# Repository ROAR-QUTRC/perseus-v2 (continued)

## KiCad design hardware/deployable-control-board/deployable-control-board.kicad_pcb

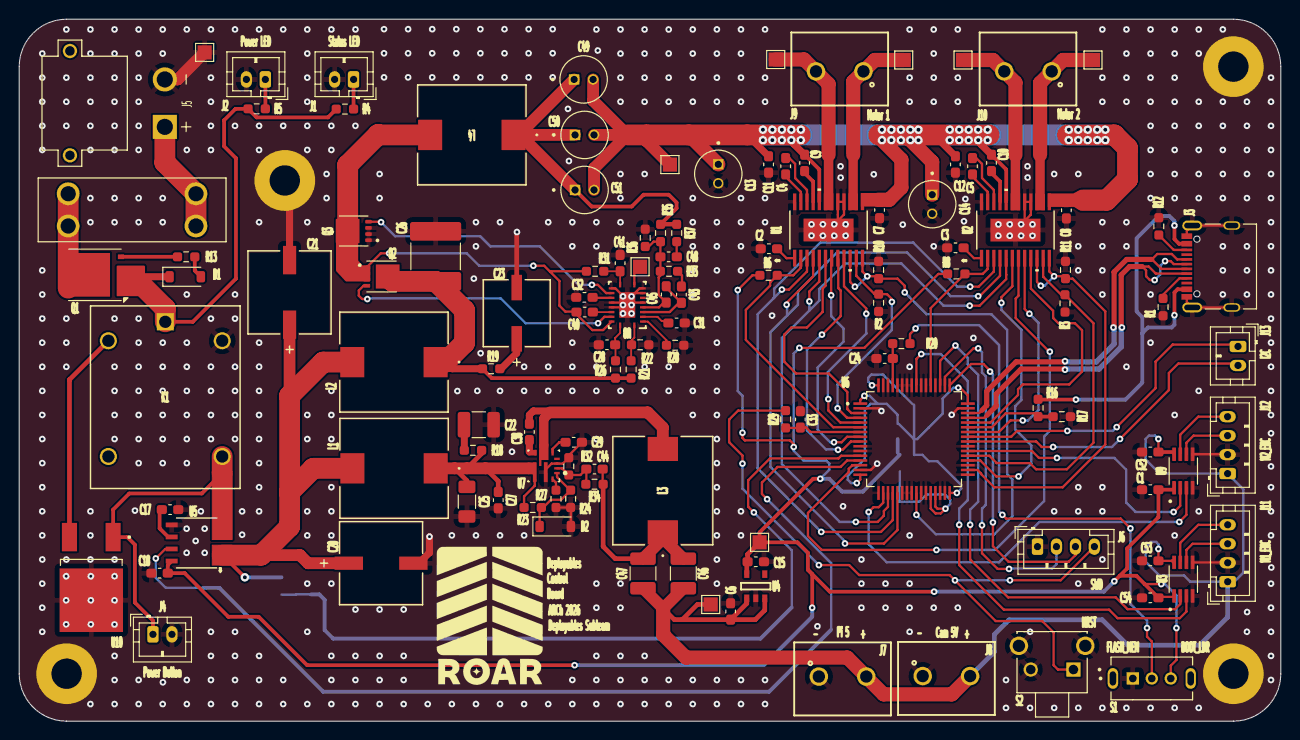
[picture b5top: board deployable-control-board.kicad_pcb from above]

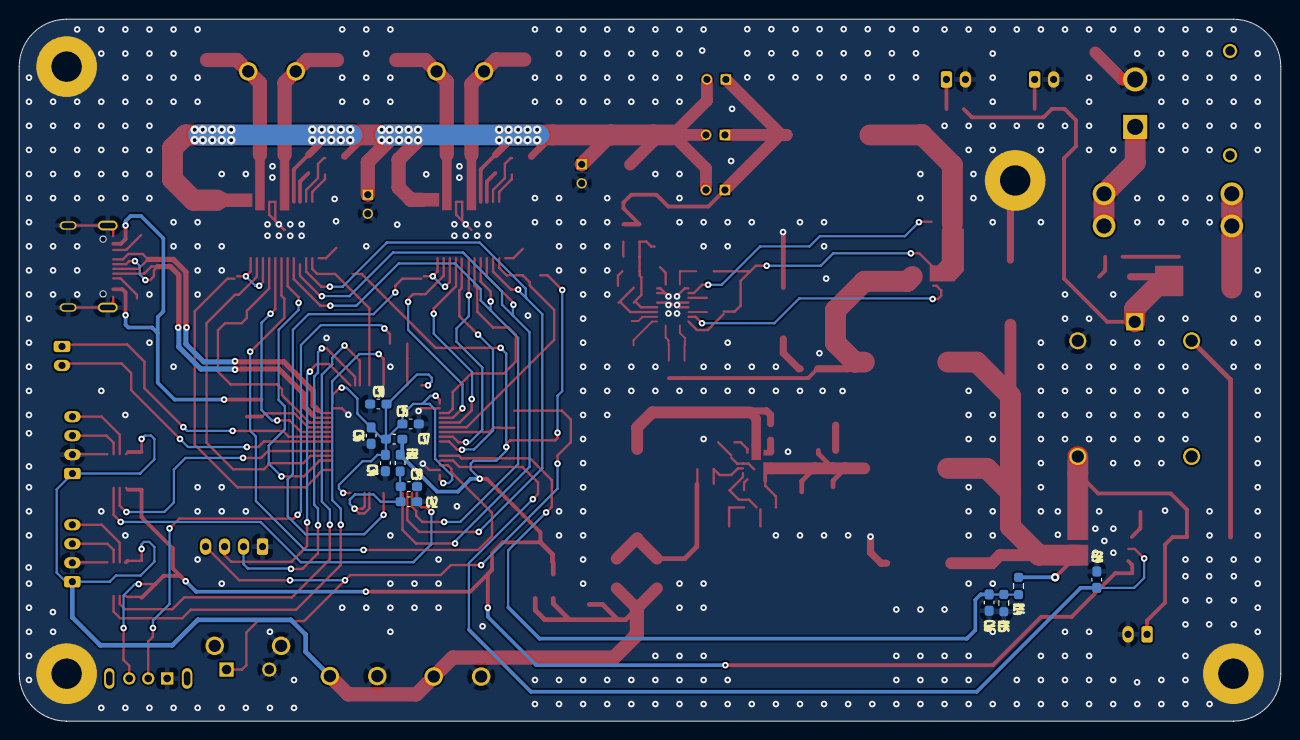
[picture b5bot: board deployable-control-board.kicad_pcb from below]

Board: 2 copper layers, 133.0 x 74.0 mm, 135 parts (12 on the bottom side), 97 nets.

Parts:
3.2mm, 3.2mm#2: MountingHole_3.2mm_M3_Pad
C1, C7, C8, C11, C16, C18, C24, C28, C30, C33, C34, C35, C36, C38, C39, C40, C52, C53, C54: 100n; C_0603_1608Metric_Pad1.08x0.95mm_HandSolder
C2, C3, C6, C9, C10, C12, C15, C27, C42: 1u; C_0603_1608Metric_Pad1.08x0.95mm_HandSolder
C4, C5: 47n; C_0603_1608Metric_Pad1.08x0.95mm_HandSolder
C13, C14, C49, C50, C51: 22u; CAPPRD200W50D500H1100
C17: 1n; C_0603_1608Metric_Pad1.08x0.95mm_HandSolder
C19: 10n; C_0603_1608Metric_Pad1.08x0.95mm_HandSolder
C20, C21: 180u; PCAP_SVP_E12_PAN-L
C22: 10u; C_1210_3225Metric_Pad1.33x2.70mm_HandSolder
C23: 47u; PCAP_SVP_C6_PAN-L
C25: 15u; C_1206_3216Metric_Pad1.33x1.80mm_HandSolder
C26: 15u; C_2220_5750Metric_Pad1.97x5.40mm_HandSolder
C29: 22n; C_0603_1608Metric_Pad1.08x0.95mm_HandSolder
C31: 56n; C_0603_1608Metric_Pad1.08x0.95mm_HandSolder
C32: 2u2; C_0603_1608Metric_Pad1.08x0.95mm_HandSolder
C37: 4u7; C_0603_1608Metric_Pad1.08x0.95mm_HandSolder
C41: 10p; C_0603_1608Metric_Pad1.08x0.95mm_HandSolder
C43: 12n; C_0603_1608Metric_Pad1.08x0.95mm_HandSolder
C44: 150p; C_0603_1608Metric_Pad1.08x0.95mm_HandSolder
C45: 1n5; C_0603_1608Metric_Pad1.08x0.95mm_HandSolder
C46, C47: 22u; C_1210_3225Metric_Pad1.33x2.70mm_HandSolder
C48: 560p; C_0603_1608Metric_Pad1.08x0.95mm_HandSolder
D1: 12V; D_SOD-123
D2: D_Zener; D_SOD-123
F1: 20A; FUSE_3557-10
FB1: FerriteBead; L_0603_1608Metric_Pad1.05x0.95mm_HandSolder
J1: Status LED; JST_PH_B2B-PH-K_1x02_P2.00mm_Vertical
J2: Power LED; JST_PH_B2B-PH-K_1x02_P2.00mm_Vertical
J3: 12402012E212A; AMPHENOL_12402012E212A
J4: Power Button; JST_PH_B2B-PH-K_1x02_P2.00mm_Vertical
J5: XT30PW-M; AMASS_XT30PW-M
J6: SWD; JST_PH_B4B-PH-K_1x04_P2.00mm_Vertical
J7: RPi_PWR; 691137710002
J8: CAMERA; 691137710002
J9: M1_PWR; 691137710002
J10: M2_PWR; 691137710002
J11: M1_ENC; JST_PH_B4B-PH-K_1x04_P2.00mm_Vertical
J12: M2_ENC; JST_PH_B4B-PH-K_1x04_P2.00mm_Vertical
J13: I2C; JST_PH_B2B-PH-K_1x02_P2.00mm_Vertical
K1: J107F1CS125VDC.36; RELAY5_J107F-1C_CRS
L1: 4u7; IND_IHLP-4040DZ_VIS-L
L2: 1u8; IND_IHLP-4040DZ_VIS-L
L3: 3u3; IND_IHLP-4040DZ_VIS-L
L4: 5u6; IND_IHLP-4040DZ_VIS-L
Q1: AON6411; AO_DFN-8-1EP_5.55x5.2mm_P1.27mm_EP4.12x4.6mm
Q2: CSD17577Q3A; MOSFET_CSD17577Q3A
Q3: CSD17578Q3A; TRANS_CSD18543Q3A
R1, R12: 5k1; R_0603_1608Metric_Pad0.98x0.95mm_HandSolder
R2, R3: DNP; R_0603_1608Metric_Pad0.98x0.95mm_HandSolder
R4: R; R_0603_1608Metric_Pad0.98x0.95mm_HandSolder
R5: 470; R_0603_1608Metric_Pad0.98x0.95mm_HandSolder
R6, R8, R14, R17, R20, R32: 10k; R_0603_1608Metric_Pad0.98x0.95mm_HandSolder
R10, R11: 360; R_0603_1608Metric_Pad0.98x0.95mm_HandSolder
R13: 22k; R_0603_1608Metric_Pad0.98x0.95mm_HandSolder
R15: 3k9; R_0603_1608Metric_Pad0.98x0.95mm_HandSolder
R16: 4k7; R_0603_1608Metric_Pad0.98x0.95mm_HandSolder
R18: 1; R_0603_1608Metric_Pad0.98x0.95mm_HandSolder
R19: 360m; R_0603_1608Metric_Pad0.98x0.95mm_HandSolder
R21: 68k1; R_0603_1608Metric_Pad0.98x0.95mm_HandSolder
R22: 9k1; R_0603_1608Metric_Pad0.98x0.95mm_HandSolder
R23: 3k09; R_0603_1608Metric_Pad0.98x0.95mm_HandSolder
R24: 294; R_0603_1608Metric_Pad0.98x0.95mm_HandSolder
R26: 2R1; R_0603_1608Metric_Pad0.98x0.95mm_HandSolder
R27: 52k3; R_0603_1608Metric_Pad0.98x0.95mm_HandSolder
R28: 59k; R_0603_1608Metric_Pad0.98x0.95mm_HandSolder
R29: 100; R_0603_1608Metric_Pad0.98x0.95mm_HandSolder
R31: 787; R_0603_1608Metric_Pad0.98x0.95mm_HandSolder
R33: 1k37; R_0603_1608Metric_Pad0.98x0.95mm_HandSolder
R34: 73k2; R_0603_1608Metric_Pad0.98x0.95mm_HandSolder
R35: 18k; R_0603_1608Metric_Pad0.98x0.95mm_HandSolder
R36: 1k27; R_0603_1608Metric_Pad0.98x0.95mm_HandSolder
R37: 41R2; R_0603_1608Metric_Pad0.98x0.95mm_HandSolder
S1: BOOT_SEL; SW_SLW-864587-2A-RA-N-D
S2: NRST; SW_TS11-674-50-BK-260-RA-D
TP1, TP2, TP3, TP4, TP5, TP6, TP7, TP9, TP10: TestPoint; TestPoint_Pad_1.5x1.5mm
U1, U2: DRV8873SPWPR; PWP24_TEX-M
U3, U9: SN74LVC2T45DCTR; SOP65P400X130-8N
U4: TLV75533PDBVR
U5: ACS725LLCTR-20AB-T; SOICN8_LC_ALM-L
U6: STM32G474RET6; QFP50P1200X1200X160-64N
U7: TPS56A37RPAR
U8: LM25145RGYR; IC_LM25145RGYR
U10: L78M12CDT-TR; VREG_L78M12CDT-TR

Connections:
+3.3V: C1.1, C15.2, C18.2, C37.2, C54.1, FB1.1, R6.2, R8.2, S1.3, TP6.1, U3.1 (VCCA), U4.5 (OUT), U5.8 (VCC), U9.1 (VCCA)
+5V: C6.1, C46.2, C47.2, C52.1, C53.1, J7.2, J8.2, J11.1, J12.1, TP9.1, U3.8 (VCCB), U4.1 (IN), U4.3 (EN), U9.8 (VCCB)
+12V: C7.2, C8.2, C9.2, C10.2, C11.2, C12.2, C13.P, C14.P, C49.N, C50.N, C51.N, TP10.1, U1.13 (VM), U1.20 (VM), U2.13 (VM), U2.20 (VM)
+BATT: C20.1, C21.1, L1.2, L2.2, R14.1, U5.1 (IP+), U5.2 (IP+)
/12V_PGOOD: TP7.1, U8.10 (PGOOD)
/ADC_BATT_CURR: C19.2, U5.7 (VIOUT), U6.13 (PA1)
/ADC_BATT_VOLT: C16.1, R14.2, R15.1, U6.12 (PA0)
/I2C3_SCL: J13.2, U6.40 (PC8)
/I2C3_SDA: J13.1, U6.41 (PC9)
/LED_PWR: D1.1 (K), K1.1, Q1.1 (S), Q1.2 (S), Q1.3 (S), R4.2, R5.2
/M1_DSBL: U1.9 (DISABLE), U6.5 (PF0-OSC_IN)
/M1_ENC_A: U3.2 (A1), U6.51 (PA15)
/M1_ENC_B: U3.3 (A2), U6.56 (PB3)
/M1_IN1: U1.7 (EN/IN1), U6.8 (PC0)
/M1_IN2: U1.8 (PH/IN2), U6.9 (PC1)
/M1_IPROPI: R10.2, U1.10 (IPROPI1), U1.12 (IPROPI2), U6.25 (PB1)
/M1_MOT_A: J11.4, U3.7 (B1)
/M1_MOT_B: J11.3, U3.6 (B2)
/M1_NFAULT: R6.1, U1.2 (NFAULT), U6.6 (PF1-OSC_OUT)
/M1_NSCS: U1.6 (NSCS), U6.3 (PC14-OSC32_IN)
/M1_NSLEEP: R2.2, U1.11 (NSLEEP), U6.4 (PC15-OSC32_OUT)
/M1_OUT1: J9.2, TP4.1, U1.18 (OUT1), U1.19 (OUT1)
/M1_OUT2: J9.1, TP2.1, U1.14 (OUT2), U1.15 (OUT2)
/M2_DSBL: U2.9 (DISABLE), U6.44 (PA10)
/M2_ENC_A: U6.38 (PC6), U9.2 (A1)
/M2_ENC_B: U6.18 (PA4), U9.3 (A2)
/M2_IN1: U2.7 (EN/IN1), U6.14 (PA2)
/M2_IN2: U2.8 (PH/IN2), U6.42 (PA8)
/M2_IPROPI: R11.2, U2.10 (IPROPI1), U2.12 (IPROPI2), U6.34 (PB12)
/M2_MOT_A: J12.4, U9.7 (B1)
/M2_MOT_B: J12.3, U9.6 (B2)
/M2_NFAULT: R8.1, U2.2 (NFAULT), U6.53 (PC11)
/M2_NSCS: U2.6 (NSCS), U6.36 (PB14)
/M2_NSLEEP: R3.2, U2.11 (NSLEEP), U6.37 (PB15)
/M2_OUT1: J10.2, TP5.1, U2.18 (OUT1), U2.19 (OUT1)
/M2_OUT2: J10.1, TP3.1, U2.14 (OUT2), U2.15 (OUT2)
/NRST: J6.4, R29.2, S2.1
/SPI1_CLK: U1.5 (SCLK), U2.5 (SCLK), U6.19 (PA5)
/SPI1_MISO: U1.3 (SDO), U2.3 (SDO), U6.20 (PA6)
/SPI1_MOSI: U1.4 (SDI), U2.4 (SDI), U6.21 (PA7)
/SWCLK: J6.3, U6.49 (PA13)
/SWDIO: J6.2, U6.50 (PA14)
/USB_D+: J3.A6 (D+_A), J3.B6 (D+_B), U6.46 (PA12)
/USB_D-: J3.A7 (D-_A), J3.B7 (D-_B), U6.45 (PA11)
/USB_VBUS: R16.2, R17.1, U6.43 (PA9)
/VBUS: J3.A4_B9 (VBUS), J3.B4_A9 (VBUS__1), R16.1
GND: 3.2mm.1, 3.2mm#2.1, C1.2, C2.2, C3.2, C6.2, C7.1, C8.1, C11.1, C12.1, C13.N, C14.N, C15.1, C16.2, C17.2, C18.1, C19.1, C20.2, C21.2, C22.2, C23.2, C24.2, C25.2, C26.2, C27.2, C28.2, C29.1, C30.1, C31.1, C32.1, C33.2, C34.1, C35.1, C36.1, C39.1, C41.1, C42.1, C52.2, C53.2, C54.2, D2.2 (A), J1.2, J2.2, J3.A1_B12 (GND), J3.B1_A12 (GND__1), J3.SH1 (SHIELD), J3.SH2 (SHIELD__1), J3.SH3 (SHIELD__2), J3.SH4 (SHIELD__3), J4.2, J5.N, J6.1, J7.1, J8.1, J11.2, J12.2, K1.5, Q3.1 (S1), Q3.2 (S2), Q3.3 (S3), R1.1, R2.1, R3.1, R10.1, R11.1, R12.2, R15.2, R17.2, R22.2, R24.2, R27.1, R28.2, R32.2, R36.2, S1.1, S2.2, S2.3 (GND), S2.4 (GND__1), TP1.1, U1.16 (SRC), U1.17 (SRC), U1.24 (GND), U1.25 (EPAD), U2.16 (SRC), U2.17 (SRC), U2.24 (GND), U2.25 (EPAD), U3.4 (GND), U3.5 (DIR), U4.2 (GND), U5.5 (GND), U6.2 (PC13), U6.10 (PC2), U6.11 (PC3), U6.15 (VSS), U6.17 (PA3), U6.22 (PC4), U6.23 (PC5), U6.24 (PB0), U6.26 (PB2), U6.27 (VSSA), U6.30 (PB10), U6.31 (VSS__1), U6.33 (PB11), U6.35 (PB13), U6.39 (PC7), U6.47 (VSS__2), U6.52 (PC10), U6.54 (PC12), U6.55 (PD2), U6.57 (PB4), U6.58 (PB5), U6.59 (PB6), U6.60 (PB7), U6.62 (PB9), U6.63 (VSS__3), U7.3 (AGND), U7.9 (PGND), U8.6 (AGND), U8.8 (SYNCIN), U8.9 (NC), U8.12 (PGND), U8.15 (EP), U8.16 (NC), U8.21 (EP), U9.4 (GND), U9.5 (DIR), U10.2 (GND)
unnamed: C22.1, R18.2
unnamed: C23.1, R19.2
unnamed: C43.2, R33.1
unnamed: C44.1, C46.1, C47.1, L3.1, R34.1
unnamed: C48.1, R37.2
unnamed: C49.P, C50.P, C51.P, L4.1, R35.1, R37.1
unnamed: D1.2 (A), R13.2
unnamed: D2.1 (K), R23.2, R24.1, U7.1 (EN)
unnamed: F1.1_1, F1.1_2, J5.P
unnamed: J1.1, R4.1
unnamed: J2.1, R5.1
unnamed: J3.A5 (CC1_A), R1.2
unnamed: J3.B5 (CC1_B), R12.1
unnamed: J4.1, K1.4, U5.3 (IP-), U5.4 (IP-), U10.1 (IN)
unnamed: F1.2_1, F1.2_2, Q1.5 (D)
unnamed: Q1.4 (G), R13.1
unnamed: C40.2, L4.2, Q2.1, Q2.2, Q2.3, Q3.5 (D5), R31.2, U8.19 (SW)
unnamed: Q3.4 (G), U8.13 (LO)
unnamed: R20.1, S1.2
unnamed: C4.2, U1.22 (CPH)
unnamed: C4.1, U1.23 (CPL)
unnamed: C2.1, U1.1 (DVDD)
unnamed: C9.1, U1.21 (VCP)
unnamed: C5.2, U2.22 (CPH)
unnamed: C5.1, U2.23 (CPL)
unnamed: C3.1, U2.1 (DVDD)
unnamed: C10.1, U2.21 (VCP)
unnamed: C17.1, U5.6 (FILTER)
unnamed: C24.1, R20.2, U6.61 (PB8-BOOT0)
unnamed: C33.1, R29.1, U6.7 (PG10-~RST)
unnamed: C30.2, C34.2, C35.2, C36.2, C37.1, U6.1 (VBAT), U6.16 (VDD), U6.32 (VDD__1), U6.48 (VDD__2), U6.64 (VDD__3)
unnamed: C39.2, C42.2, FB1.2, U6.28 (VREF+), U6.29 (VDDA)
unnamed: C38.1, U7.7 (BOOT)
unnamed: C44.2, R32.1, R34.2, U7.2 (FB)
unnamed: R27.2, U7.10 (MODE)
unnamed: C29.2, U7.5 (SS)
unnamed: C38.2, L3.2, U7.6 (SW)
unnamed: C40.1, U8.17 (BST)
unnamed: C43.1, C45.1, U8.4 (COMP)
unnamed: R21.2, R22.1, U8.1 (EN_UVLO)
unnamed: C45.2, C48.2, R33.2, R35.2, R36.1, U8.5 (FB)
unnamed: Q2.4, U8.18 (HO)
unnamed: C41.2, R31.1, U8.11 (ILIM)
unnamed: R28.1, U8.2 (RT)
unnamed: C31.2, U8.3 (SS_TRK)
unnamed: C32.2, U8.14 (VCC)
unnamed: C28.1, R26.2, U8.20 (VIN)
unnamed: K1.2, U10.3 (OUT)
VBAT_5V: C25.1, C27.1, L1.1, R18.1, R23.1, U7.8 (VIN)
VBAT_12V: C26.1, L2.1, Q2.9, R19.1, R21.1, R26.1

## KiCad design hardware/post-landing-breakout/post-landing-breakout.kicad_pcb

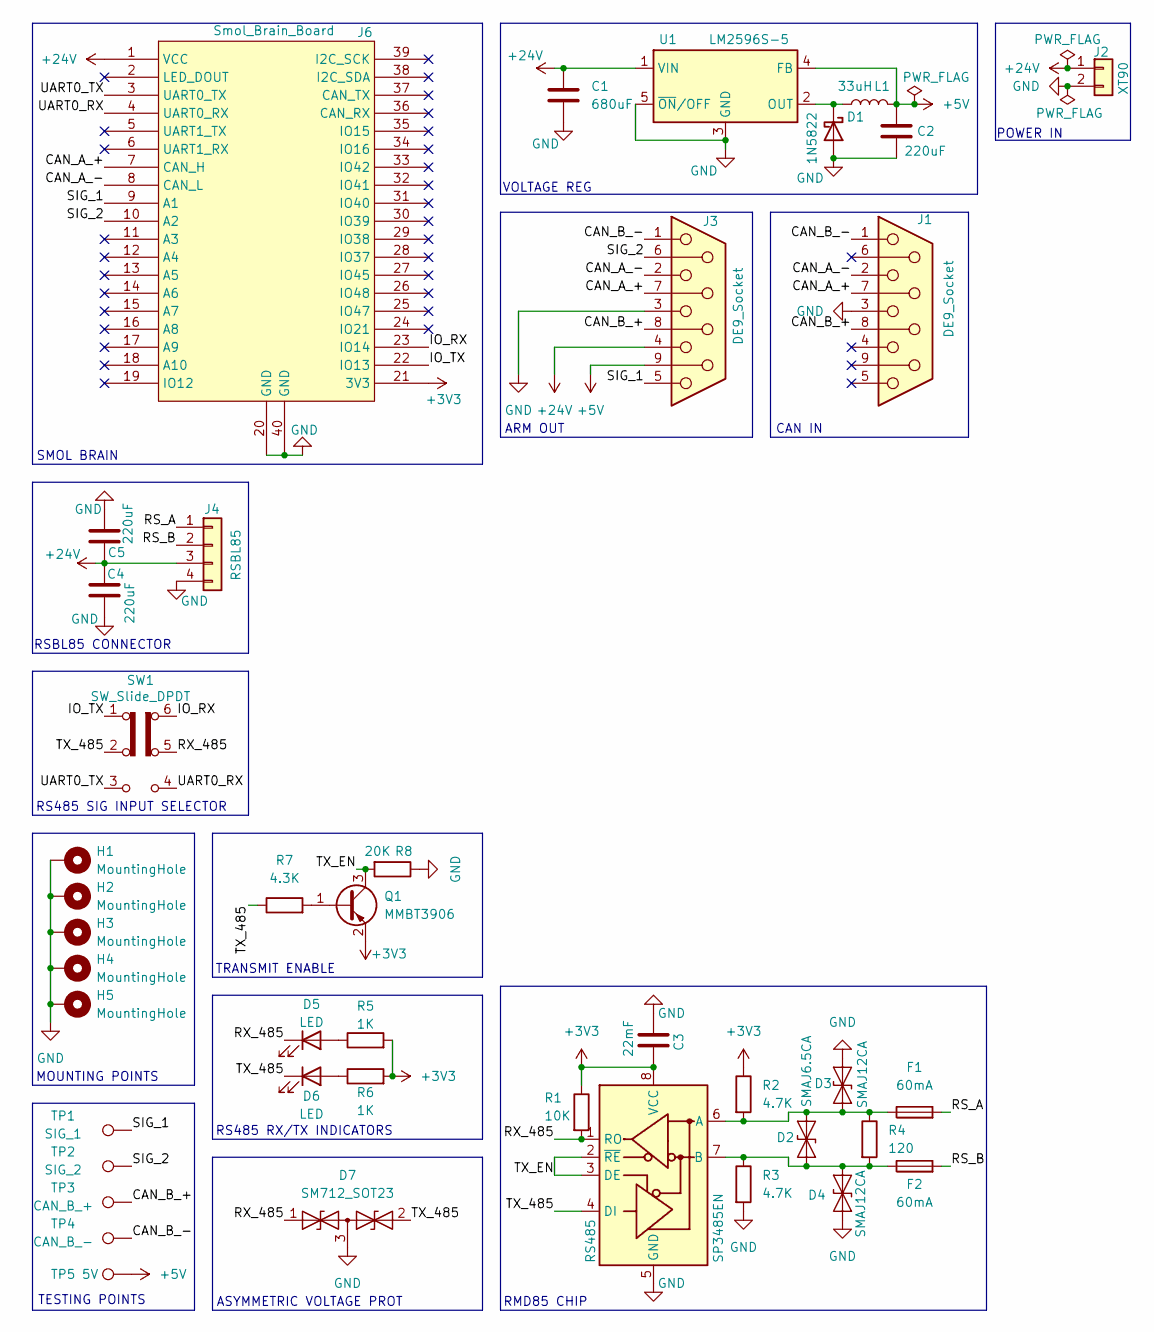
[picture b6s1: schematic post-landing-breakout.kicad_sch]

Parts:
C1: 680uF; C_0805_2012Metric_Pad1.18x1.45mm_HandSolder
C2: 220uF; C_0805_2012Metric_Pad1.18x1.45mm_HandSolder
C3: 22mF; C_0805_2012Metric_Pad1.18x1.45mm_HandSolder
C4, C5: 220uF; CP_Radial_D8.0mm_P3.50mm
D1: 1N5822; D_DO-201AD_P15.24mm_Horizontal
D2: SMAJ6.5CA; D_SMA
D3, D4: SMAJ12CA; D_SMA
D5, D6: LED; LED_0805_2012Metric_Pad1.15x1.40mm_HandSolder
D7: SM712_SOT23; SOT-23
F1, F2: 60mA; Fuse_0805_2012Metric_Pad1.15x1.40mm_HandSolder
H1, H2, H3, H4, H5: MountingHole; MountingHole_3mm_Pad_TopBottom
J1, J3: DE9_Socket; DSUB-9_Socket_Horizontal_P2.77x2.84mm_EdgePinOffset4.94mm_H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
J2: XT90; AMASS_XT90PW-M_1x02_P10.90mm_Horizontal
J4: RSBL85; JST_ZH_B4B-ZR_1x04_P1.50mm_Vertical
J6: Smol_Brain_Board
L1: 33uH; L_Vishay_IHLP-5050
Q1: MMBT3906; SOT-23
R1: 10K; R_0805_2012Metric_Pad1.20x1.40mm_HandSolder
R2, R3: 4.7K; R_0805_2012Metric_Pad1.20x1.40mm_HandSolder
R4: 120; R_0805_2012Metric_Pad1.20x1.40mm_HandSolder
R5, R6: 1K; R_0805_2012Metric_Pad1.20x1.40mm_HandSolder
R7: 4.3K; R_0805_2012Metric_Pad1.20x1.40mm_HandSolder
R8: 20K; R_0805_2012Metric_Pad1.20x1.40mm_HandSolder
RS485: SP3485EN; SOIC-8_3.9x4.9mm_P1.27mm
SW1: SW_Slide_DPDT; SW_CK_JS202011CQN_DPDT_Straight
TP1: SIG_1; TestPoint_THTPad_1.5x1.5mm_Drill0.7mm
TP2: SIG_2; TestPoint_THTPad_1.5x1.5mm_Drill0.7mm
TP3: CAN_B_+; TestPoint_THTPad_1.5x1.5mm_Drill0.7mm
TP4: CAN_B_-; TestPoint_THTPad_1.5x1.5mm_Drill0.7mm
TP5: 5V; TestPoint_THTPad_1.5x1.5mm_Drill0.7mm
U1: LM2596S-5; TO-263-5_TabPin3

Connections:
+3V3: C3.1, J6.21 (3V3), Q1.2 (E), R1.1, R2.1, R5.2, R6.2, RS485.8 (VCC)
+5V: C2.1, J3.9, L1.2, TP5.1, U1.4 (FB)
+24V: C1.1, C4.1, C5.1, J2.1, J3.4, J4.3, J6.1 (VCC), U1.1 (VIN)
/CAN_A_+: J1.7, J3.7, J6.7 (CAN_H)
/CAN_A_-: J1.2, J3.2, J6.8 (CAN_L)
/CAN_B_+: J1.8, J3.8, TP3.1
/CAN_B_-: J1.1, J3.1, TP4.1
/IO_RX: J6.23 (IO14), SW1.6 (C)
/IO_TX: J6.22 (IO13), SW1.1 (A)
/RS_A: F1.2, J4.1
/RS_B: F2.2, J4.2
/RX_485: D5.1 (K), D7.1 (A1), R1.2, RS485.1 (RO), SW1.5 (B)
/SIG_1: J3.5, J6.9 (A1), TP1.1
/SIG_2: J3.6, J6.10 (A2), TP2.1
/TX_485: D6.1 (K), D7.2 (A2), R7.1, RS485.4 (DI), SW1.2 (B)
/TX_EN: Q1.3 (C), R8.2, RS485.2 (~RE), RS485.3 (DE)
/UART0_RX: J6.4 (UART0_RX), SW1.4 (A)
/UART0_TX: J6.3 (UART0_TX), SW1.3 (C)
GND: C1.2, C2.2, C3.2, C4.2, C5.2, D1.2 (A), D3.2 (A2), D4.2 (A2), D7.3 (common), H1.1, H2.1, H3.1, H4.1, H5.1, J1.3, J2.2, J3.3, J4.4, J6.20 (GND), J6.40 (GND), R3.2, R8.1, RS485.5 (GND), U1.3 (GND), U1.5 (~ON/OFF)
unnamed: D1.1 (K), L1.1, U1.2 (OUT)
unnamed: D2.1 (A1), D4.1 (A1), F2.1, R3.1, R4.2, RS485.7 (B)
unnamed: D2.2 (A2), D3.1 (A1), F1.1, R2.2, R4.1, RS485.6 (A)
unnamed: D5.2 (A), R5.1
unnamed: D6.2 (A), R6.1
unnamed: Q1.1 (B), R7.2

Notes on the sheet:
MOUNTING POINTS
POWER IN
CAN IN
RS485 RX/TX INDICATORS
SMOL BRAIN
ARM OUT
RSBL85 CONNECTOR
VOLTAGE REG
TESTING POINTS
RMD85 CHIP
RS485 SIG INPUT SELECTOR
ASYMMETRIC VOLTAGE PROT
TRANSMIT ENABLE

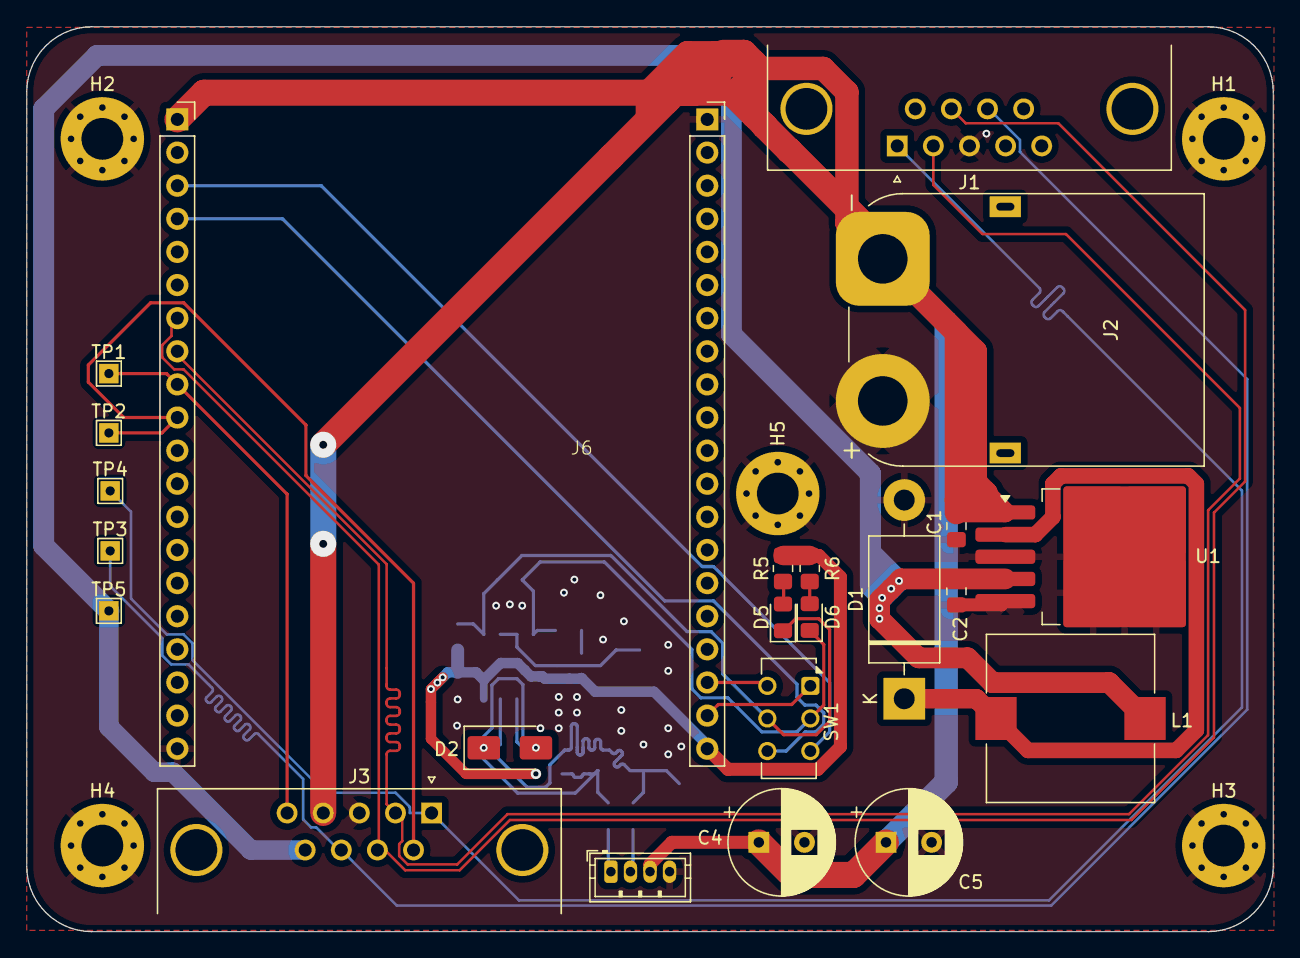
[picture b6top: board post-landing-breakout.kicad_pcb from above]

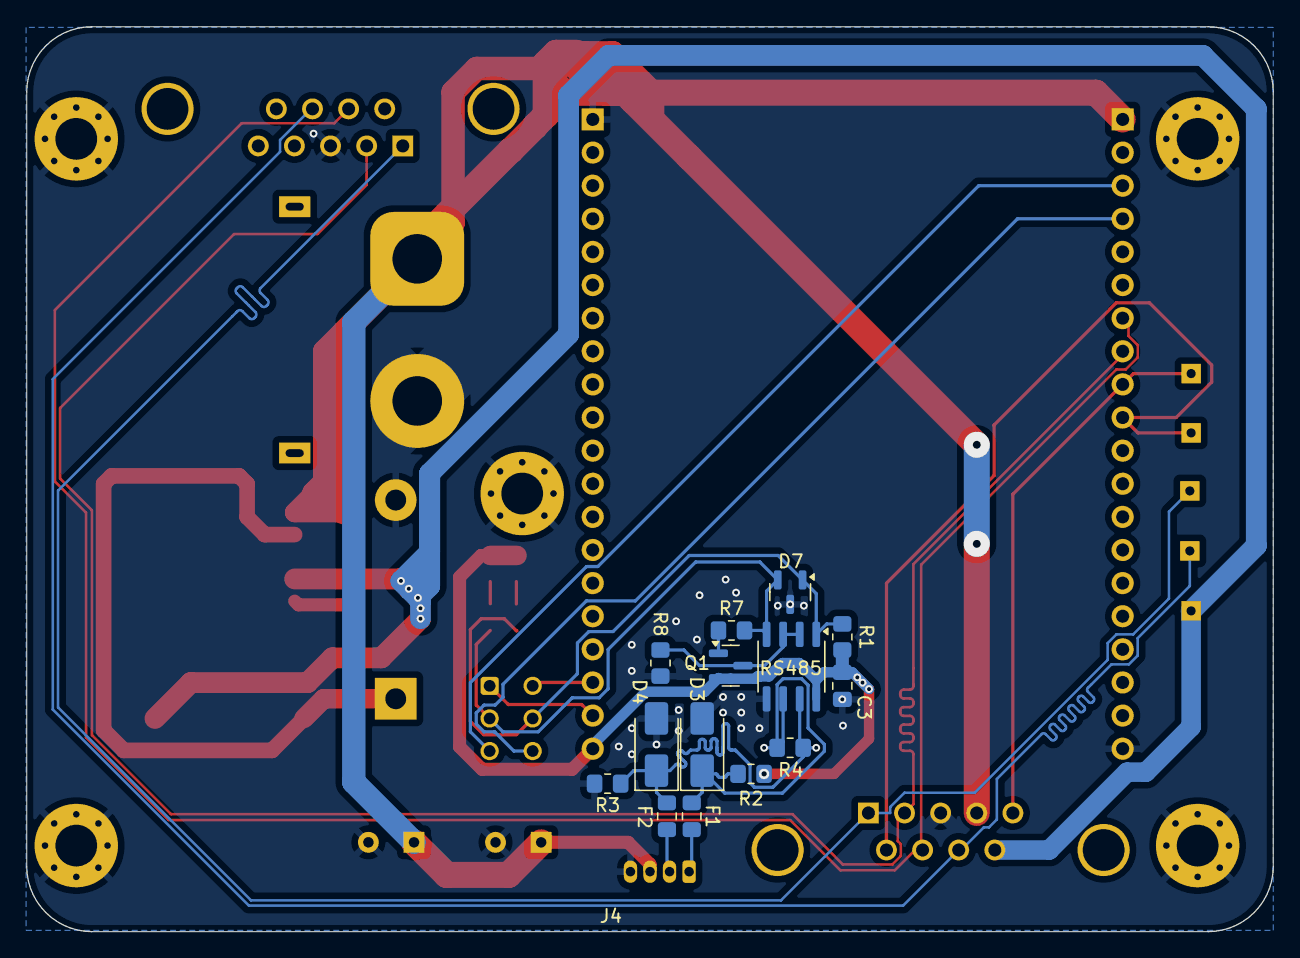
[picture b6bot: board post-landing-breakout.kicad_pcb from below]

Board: 2 copper layers, 95.6 x 69.4 mm, 42 parts (14 on the bottom side), 25 nets.

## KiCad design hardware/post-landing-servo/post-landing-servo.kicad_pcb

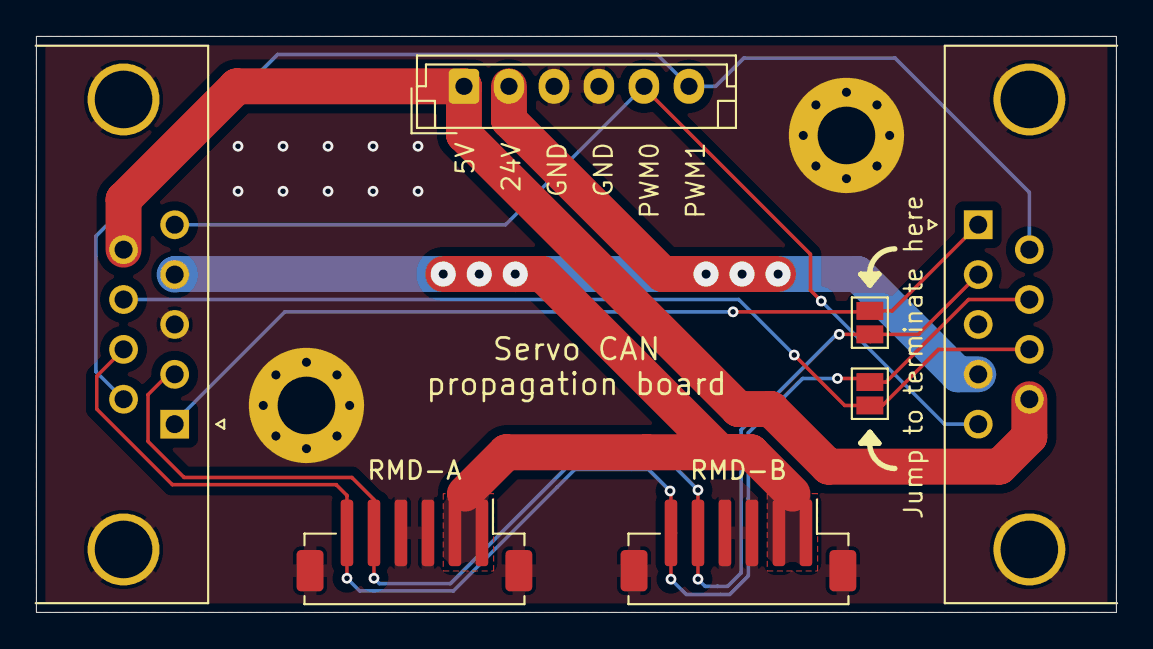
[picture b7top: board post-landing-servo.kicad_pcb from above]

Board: 2 copper layers, 60.0 x 32.0 mm, 9 parts (0 on the bottom side), 9 nets.

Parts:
5V    24V   GND    PWM1 PWM2: Conn_01x06; JST_EH_B6B-EH-A_1x06_P2.50mm_Vertical
H3, H4: MountingHole_Pad; MountingHole_3.2mm_M3_Pad_Via
J9, J10: DE9_Socket; DSUB-9_Socket_Horizontal_P2.77x2.84mm_EdgePinOffset4.94mm_H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
JP3, JP4: SolderJumper_2_Open; SolderJumper-2_P1.3mm_Open_Pad1.0x1.5mm
RMD-A: Conn_01x06; JST_ZH_B6B-ZR-SM4-TF_1x06-1MP_P1.50mm_Vertical
RMD-B: Conn_01x06; JST_ZH_B6B-ZR-SM4-TF_1x06-1MP_P1.50mm_Vertical

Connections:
+5V: 5V 24V GND PWM1 PWM2.1, J9.9, J10.9
+24V: 5V 24V GND PWM1 PWM2.2, J9.4, J10.4, RMD-A.1, RMD-A.2, RMD-B.1, RMD-B.2
/CAN_A+: J9.7, J10.7, JP4.1 (A), RMD-A.6, RMD-B.6
/CAN_A-: J9.2, J10.2, JP3.1 (A), RMD-A.5, RMD-B.5
/CAN_B+: J9.8, J10.8, JP4.2 (B)
/CAN_B-: J9.1, J10.1, JP3.2 (B)
/SIG1: 5V 24V GND PWM1 PWM2.5, J9.5, J10.5
/SIG2: 5V 24V GND PWM1 PWM2.6, J9.6, J10.6
GND: 5V 24V GND PWM1 PWM2.3, 5V 24V GND PWM1 PWM2.4, H3.1, H4.1, J9.0 (PAD), J9.3, J10.0 (PAD), J10.3, RMD-A.3, RMD-A.4, RMD-A.MP, RMD-B.3, RMD-B.4, RMD-B.MP
